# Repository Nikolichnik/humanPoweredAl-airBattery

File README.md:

# humanPoweredAl-airBattery
<h4>Simple Al-air battery operating, in part, thanks to specific characteristics of human skin.</h4>

It has a built-in Joule thief circuit that lights up small LED every once in a while.

<hr>

<p align="center">
  
</p>

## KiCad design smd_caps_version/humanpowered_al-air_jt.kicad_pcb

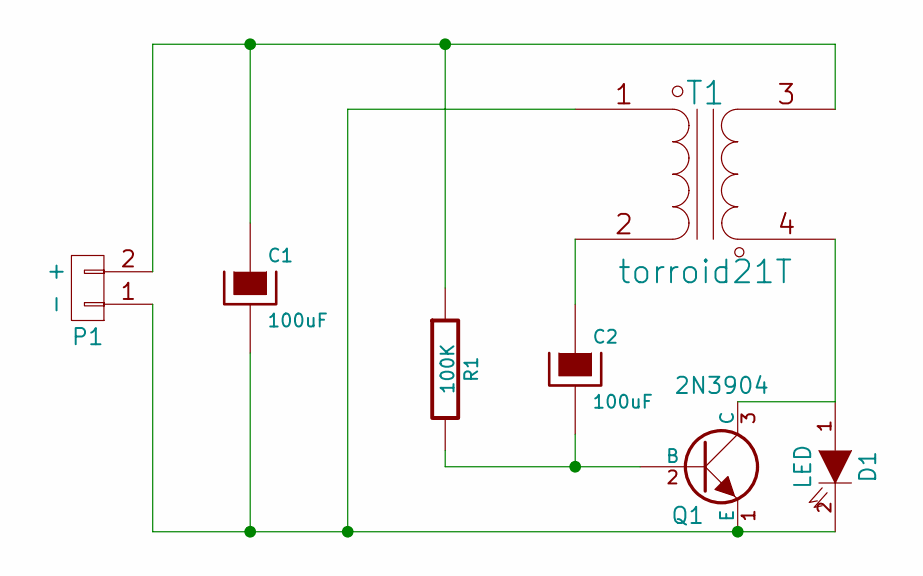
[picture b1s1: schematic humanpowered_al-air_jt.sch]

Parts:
C1, C2: 100uF; Elko_vert_11x5mm_RM2.5
D1: LED; LED-5MM
P1: - +; Pin_Header_Straight_1x02
Q1: 2N3904; sot23
R1: 100K; R_0805_HandSoldering
T1: torroid21T; Transformer_Toroid_horizontal_Diameter9mm_Amidon-T30

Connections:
unnamed: C1.1, P1.2, R1.1, T1.3 (SB)
unnamed: C1.2, D1.2 (K), P1.1, Q1.1 (E), T1.1 (AA)
unnamed: C2.1, T1.2 (AB)
unnamed: C2.2, Q1.2 (B), R1.2
unnamed: D1.1 (A), Q1.3 (C), T1.4 (SA)

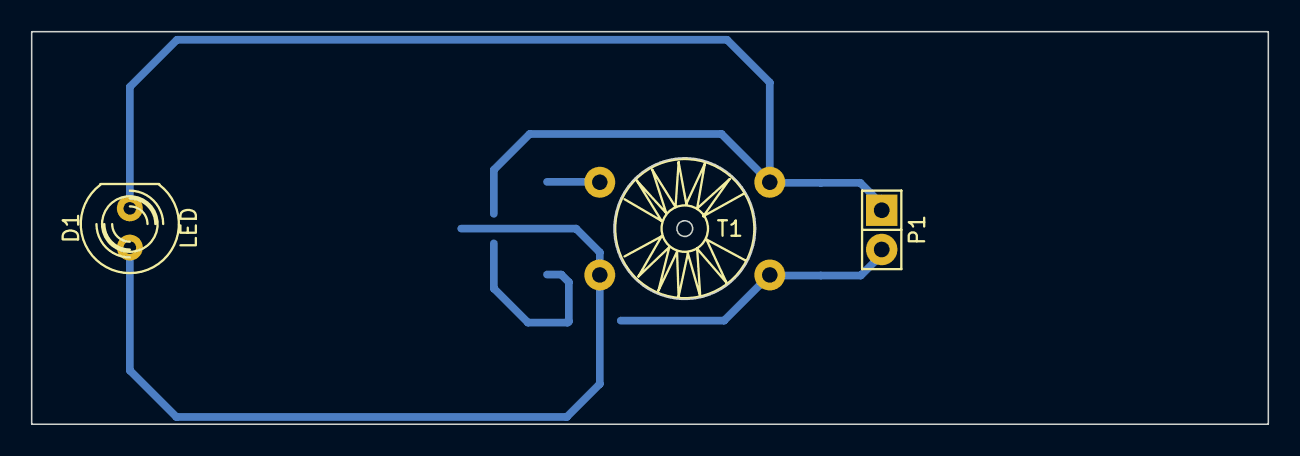
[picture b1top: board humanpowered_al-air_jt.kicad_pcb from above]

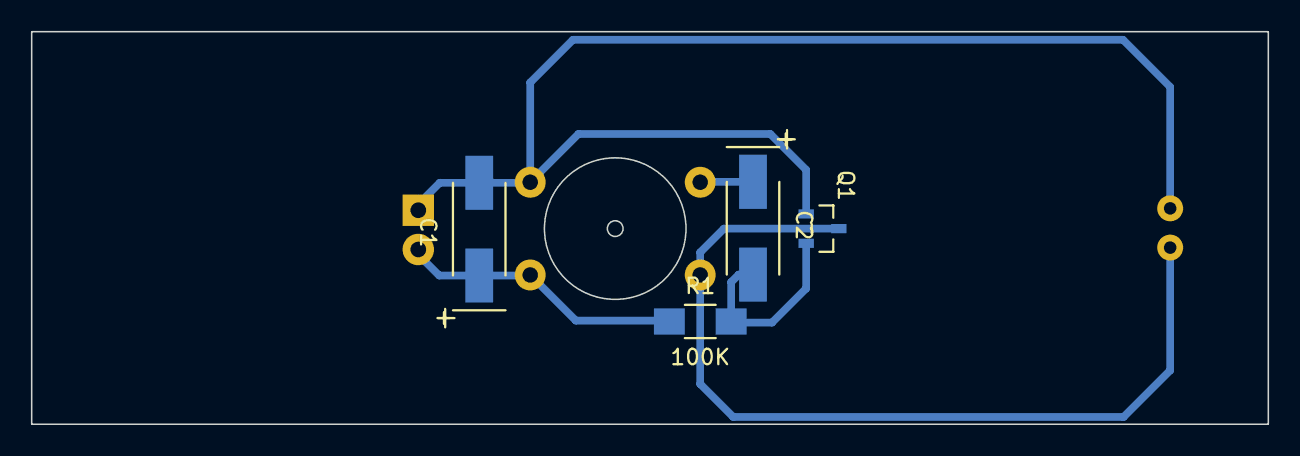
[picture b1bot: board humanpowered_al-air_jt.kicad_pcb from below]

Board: 2 copper layers, 80.0 x 25.4 mm, 7 parts (4 on the bottom side), 5 nets.
